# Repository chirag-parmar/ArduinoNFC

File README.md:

## ArduinoNFC
ArduinoNFC is a DIY security solution that uses RFID technology with the help of an Arduino. It is named NFC because it uses NFC tags in combination with RFID readers interfaced to the Arduino.

The system uses an Arduino UNO interfaced with a RFID reader that reads a tag. The EEPROM of the arduino is used to store the authorised tag values. Everytime a user brings his/her tag in front of the reader the system compares the read value with the ones stored in the database(EEPROM). The Electromagnetic Lock is controlled using a relay board, so every time the system finds a match it triggers a output pin to HIGH which inturn triggers the relay, unlocking the door. The electromagnetic lock can withstand 600lbs of force.

**NOTE: ** This system was combined with a raspberry pi running a face recognition script to increase the level of security.

*The eagle schematic and board files for the relay board design have been included.*

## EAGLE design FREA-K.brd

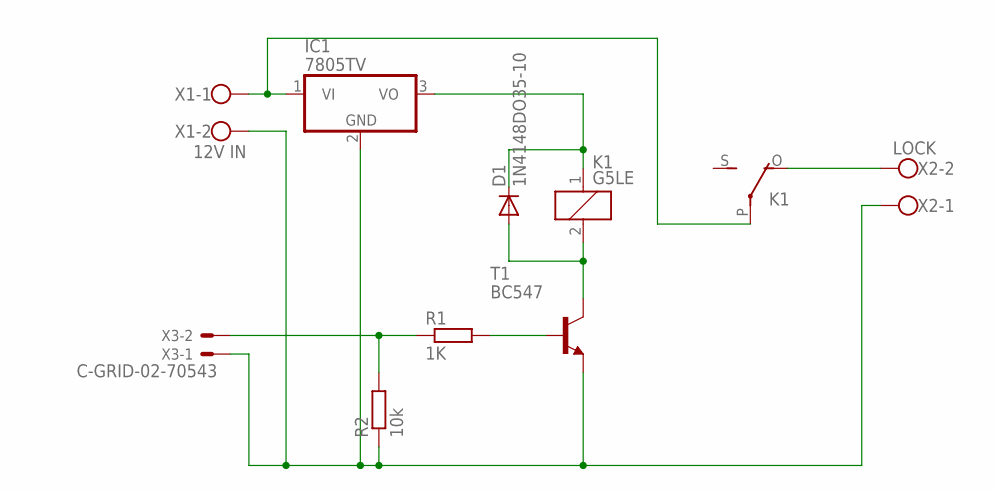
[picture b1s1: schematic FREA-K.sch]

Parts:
D1: 1N4148DO35-10; DO35-10
IC1: 7805TV; TO220V
K1: G5LE
R1: 1K; 0204/7
R2: 10k; 0204/7
T1: BC547; TO92
X1: 12V IN; W237-102
X2: LOCK; W237-102
X3: C-GRID-02-70543; 70543-02

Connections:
unnamed: D1.C, IC1.3 (VO), K1.1
unnamed: D1.A, K1.2, T1.3 (C)
unnamed: IC1.2 (GND), R2.1, T1.1 (E), X1.2, X2.1, X3.1
unnamed: R1.2, T1.2 (B)
unnamed: R1.1, R2.2, X3.2
unnamed: IC1.1 (VI), K1.P, X1.1
unnamed: K1.O, X2.2

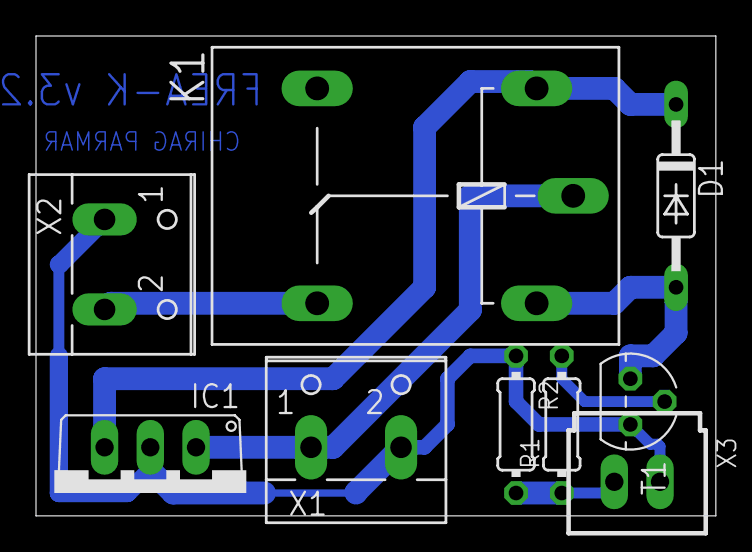
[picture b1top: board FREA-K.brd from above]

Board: 2 copper layers, 37.8 x 26.7 mm, 9 parts (0 on the bottom side), 7 nets.
